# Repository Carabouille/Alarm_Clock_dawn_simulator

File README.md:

# Alarm_Clock_dawn_simulator
Hello, I'm Carabouille, a French guy who loves tech and hardware, and this is my GitHub to present you my project for Fallout!
I'm gonna present you my alarm clock with dawn simulator feature!

AND see just how beautiful it is !!! Yeah I know I did a great job you can tell me ^^

And to see how it works in details you can watch the video that I did on my alarm clock : (CLICK ON MY AWESOME FACE !)

# The idea 
I often have trouble waking up with my phone alarm. I often feel that I'm tired even though I slept a lot. And this is for a very simple reason: our brain is not a machine, he can't wake up so fast. He works on cycles. And our phone alarm gets him off very fast during this cycle. A better way to wake up more naturally is with the solar light (but the night I close the rolling shutter for the cold). So a solution to this issue is to use an alarm clocker with a dawn simulator feature to increase the brightness of the room over time to wake up your brain gently, but problem : Tis type of alarm clocks is really expensive (over 100 euros), so I told myself that it is the perfect occasion to create my own ALARM CLOCKS WITH A DAWN SIMULATOR!!! And I'm gonna add a lot of features like: 
- local weather
- Indoor temperature / humidity
- Bedside lamp (to read the night)
- Control all the Leds in my bedroom
- and more.....

I really can't wait to build my project, develop my skills and learn so much! I'm gonna give the best version of myself to be proud of my alarm clocks and I also hope that I will have the chance to go to Shenzen to meet other hardware fans! Kind regards, your French friend, Florian "Carabouille" CHARLES :))

# Zine page 
The better way to describe my project is with a poster who talks about it! 
I'm not a good designer, but I think that I made a good poster

ET VOILA : 

The design idea is pretty simple: the alarm clock in the center and some arrows to explain the different parts of the project
I explain here 7 features: 
- The oak log for the base
- All the PCBs
- The touch screen
- The Zen river
- The light for the dawn simulator feature
- The switch on the top
- And the switches and the knob on the side

My favourite color is the pink (hard to guess ^^)
I really love the cherry flower in the background that reminds me of the cherry tree on the top of the alarm.
The UwU logo is everywhere cause with my friends it's a private joke since a few years.
I love the way that the "Fallout" goes behind the box.

Is not perfect of course but for my light skills in design I think it's really nice, I'm proud of it ! 

# CAD 
One of the main parts of my project is the CAD!
For this I used the software Solidworks ( a French soft! COCORICO!)
I'm in a toxic relationship with Solidworks, sometimes I love it, sometimes I hate it...
This software is not easy to use but after some crashes and bugs I finally made a CAD which I'm proud of

So for my project I had to work within certain constraints 

- a specific screen size
- a way to diffuse the light
- a heat sink for the light
- some buttons
- a battery
- a speaker
- a hole for the USB C port

And with all that, I need to find a good idea for design

My first idea was a shape like the giant telescope, like we can see in the American desert.
But I have never obtained a result that I like

So I completely changed my idea to have a Zen garden on the top of my alarm clock
With a tree, plants, and a river!

It looks like this : 

yes that is not the same as on the zine page,
Solidworks is not really good at rendering

But all the parts are here and I even find it cool! 
I really love that the PCB is not hidden by all the cases, it's cool to see it

On this picture we can see : the screen, the PCB, the UwU logo, the oak log and the buttons on the side

If we move to the top we can see the Zen garden 

We can see :
- The hole on the top, for the cherry tree
- The river on the front
- The switch to shut down the alarm
- The green is for the artificial moss
- and the servo motor

The servo motor is here to hide the light during the day with moss on it. And when is it the time to turn the light on the servo motor move the piece of plastic with moss on it that hides the light to let the light illuminate the room.
So the light system is invisible during the day!

The servo motor is not hidden by the case cause the moss will recover it.

And on the switch I'll put a little Japanese temple like we can see on the poster.

Let's make the walls transparent to see what is inside the box!

Yes, there are a lot of things inside it! 

We can see well in the first picture the servo motor as we saw earlier
And the light with the heat sink, which is carried by a support with screws to the box
The heat sink is necessary here cause the light needs to be at least a 8W to diffuse a minimum of the light to wake you. 
But the light is also powered on 24V and if you do the calcul

P = U * I

I = P / U

I = 8 / 24 = 0,33 A 

It's a lot for a little LED COB ! It can heat up to more than 100 degrees. With the heat sink, everything will be ok!

If we watch the second picture we can see the other components

Like the speaker, even if the light is supposed to wake you. If you sleep very deeply, good music is necessary to wake up! 
We can see on the left the PCB buttons for all the buttons and the knob. Is linked with the main PCB with a FPC cable.

The huge tank in the middle is for the water of the river. The pump is also inside. The holes are for the pipes.

We can see the USB C port in the bottom right also linked with the main PCB with a FPC cable.

On the right we have the PCB for the SD card. And below it we have our battery.
The battery is just in case that there is a power cut at home, the battery will supply the system until the return of power !

And that's already a lot for a CAD, but I'm really proud of me! I can't wait to print it!

# PCB

OK so now it's the moment to talk about my PCB! And it's a huge part of my project! 
It's only my second PCB so it's not perfect, the first was the macropad.

This is only the main PCB, and I'm going to describe all the different parts
I'm not gonna describe how I chose the components because it's not really important, but for each component I had to follow the datasheet.

So we can see at the top left the port J1 that brings the power supply from the USB C port on an other PCB.
The power is sent to the first components the MCP73871. This component charge at the same time the battery in 4,2V and supplies the system with the 5V

But 5V is too high for an ESP32, so we need to decrease it to 3,3V with the AMS1117-3.3.

For this project I used an ESP32-S3-WROOM-1 that is very powerful and the WiFi connection will help me to search for the local weather.

For the speaker, we need to use an audio amplifier. I chose to use the MAX98357A, which is very famous for this type of project

I used a DW01A and a FS8205A, this duo of components is for the battery. To avoid overload, deep discharge, and protection from the short circuit.

For the LED and the fan of the heat sink I need 24V and 12V. So I used a 2 MT3608 to increase the voltage.

To control the led I'll use 2 channels of PWM to manage the warm and cold colors of the led.
To do this I'm gonna use a 2 transistors A03400A.

I also use a VEML770 a light sensor to manage the luminosity of the screen.

We also have a lot of connectors for the : 
- Screen
- USB C
- Heat sink
- Led COB
- Led strip (to decorate)
- servo motor
- SD card PCB
- Buttons PCB
- Battery

You can see two footprint for a switch (SW3 & SW4), if you wish to switch off the main power supply or just the battery power supply (!YOU NEED TO PLACE IT ! else the circuit is open)

And after having done the wiring diagram, it's time to root all the components between them! 

This is my final solution:

We can see here all the components which I mentioned earlier
I root on 2 faces so it's not too difficult to do it. The main difficulty is to match the footprint with the real component.

And that's all for the main PCB. It's already a lot!

Let's talk about the second PCB, The Buttons PCB!! 

This PCB is simpler than the previous one, it is just a little repetitive with all the buttons 
We can see here the wiring diagram!

You can see here 4 different PCBs separated by the blue lines.
The larger is the PCB with all the buttons and the polar.
Also, I used a MCP23017 to increase the number of pins GPIO of the ESP32 ( I used a lot of buttons ^^) I'll go into detail in the firmware part. 
You can see a capacitor in parallel for each button. It's anti-bounce material. It's very important for a professional project!
I added on this PCB an AHT 20, it's a temperature and humidity sensor.

The little PCB in the middle is for the switch on the top of the box.

The PCB on the bottom is the micro SD port card PCB

and the last is the PCB for the USB C

And after this it's rooting time ! 

That wasn't possible with the dimensions I needed to avoid the waste of some part of the PCB, like you can see the part not used.
I'm gonna cut the different PCB myself with a dremel.

# Firmware
The Firmware is a big part of my project! (I said it for each part ;-;)
To code I used the software Visual Studio Code and the extension Plateformio
The code is pretty simple for the moment. I only initialize all the components. I'm gonna add all the interesting features when I could have the card in my hands.
For the moment, given that I only initialize the components, all my code parts are just from the example code that I found online and from old code that I made.

In the code I initialize :
- The I2C bus
- The audio amplifier
- The SD card
- The screen
- The wifi connection (to obtain the hour, date and more soon)
- All the buttons with the MCP23017
- Servo motor
- the EC11
- The signal PWM for the LED
- The dislay of the hours on the screen
- The enable pin for the MT3608
- The VEML7700
- The AHT20

There are still a lot of things to add. I will add this later (with components in front of me) cause it is code more complicated, and it's useless to code this without debugging in live (I guess)

The things that I need to add: 
- A good design of the hours, temperatures, etc...
- alarm features (with the dawn simulator)
- all the buttons feature like :
- - turn on the smart plug of my computer
  - play a ACNL music
  - a sleep mode
  - song chill
  - bedside lamp
  - nap timer
  - switch that shuts down the alarm
  - set alarm 1
  - set alarm 2
  - turn on the leds of my room
  - turn on the river
  - the other buttons will be there to adjust certain settings

# BOM

Now it's the time to do the BOM and order all our components! 

I mainly used this site : 

- https://www.lcsc.com/ for the components CMD
- https://www.aliexpress.com for some electronics and decoration
- https://jlcpcb.com for the PCB

I split the BOM into different parts.

The first part is the components that I'm going to order on LCSC (Overall, these are the CMD components)

| Components LCSC :               | name                    | value           | Quantity | LCSC code / link        | price (€) |                                  |
|---------------------------------|-------------------------|-----------------|----------|-------------------------|-----------|----------------------------------|
|                                 | Resistance              | 100             | 1        | [C105588](https://www.lcsc.com/product-detail/C105588.html)            | 0.13      |       X                          |
|                                 |                         | 300             | 1        | [C2930092](https://www.lcsc.com/product-detail/C2930092.html)          | 0.12      | X                                |
|                                 |                         | 5,1k            | 2        | [C2907044](https://www.lcsc.com/product-detail/C2907044.html)                | 0.11      |       X                          |
|                                 |                         | 1M              | 1        | [C2907115](https://www.lcsc.com/product-detail/C2907115.html)                | 0.08      |    X                             |
|                                 |                         | 10k             | 11       | [C98220](https://www.lcsc.com/product-detail/C98220.html)                  | 0.28      |    X                             |
|                                 |                         | 180k            | 1        | [C2906999](https://www.lcsc.com/product-detail/C2906999.html)                | 0.1       |    X                             |
|                                 |                         | 1k              | 5        | [C22548](https://www.lcsc.com/product-detail/C22548.html)                  | 0.14      |    X                             |
|                                 |                         | 390k            | 1        | [C137735](https://www.lcsc.com/product-detail/C137735)                 | 0.15      |    X                             |
|                                 |                         | 2,2k            | 2        | [C4190](https://www.lcsc.com/product-detail/C4190.html)                   | 0.14      |    X                             |
|                                 | Capacitor               | 10n             | 2        | [C100042](https://www.lcsc.com/product-detail/C100042.html)                 | 0.23      |    X                             |
|                                 |                         | 100n            | 26       | [C14663](https://www.lcsc.com/product-detail/C14663.html)                  | 0.56      |    X                             |
|                                 |                         | 10u             | 4        | [C440198](https://www.lcsc.com/product-detail/C440198.html)                 | 1.27      |    X                             |
|                                 |                         | 1u              | 1        | [C28323](https://www.lcsc.com/product-detail/C28323.html)                  | 0.24      |    X                             |
|                                 |                         | 22u             | 5        | [C342620](https://www.lcsc.com/product-detail/C342620.html)                 | 2.1       |    X                             |
|                                 |                         | 4,7u            | 2        | [C98192](https://www.lcsc.com/product-detail/C98192.html)                  | 0.18      |    X                             |
|                                 | VEML7700-TT             | X               | 1        | [C1850416](https://www.lcsc.com/product-detail/C1850416.html)                | 1.49      |    X                             |
|                                 | FS8205A                 | X               | 1        | [C2830320](https://www.lcsc.com/product-detail/C2830320.html)                | 0.52      |    X                             |
|                                 | YLED0603B (led)         | Blue            | 1        | [C19171394](https://www.lcsc.com/product-detail/C19171394.html)               | 0.54      |    X                             |
|                                 | YLED0603G (led)         | Green           | 1        | [C19273151](https://www.lcsc.com/product-detail/C19273151.html)               | 0.54      |    X                             |
|                                 | KT-0603R (led)          | Red             | 1        | [C2286](https://www.lcsc.com/product-detail/C2286.html)                   | 0.59      |    X                             |
|                                 | MAX98357AETE+T          | X               | 1        | [C910544](https://www.lcsc.com/product-detail/C910544.html)                 | 1.24      |    X                             |
|                                 | MCP73871-2AAI/ML        | X               | 1        | [C144351](https://www.lcsc.com/product-detail/C144351.html)                 | 2.74      |    X                             |
|                                 | MT3608                  | X               | 2        | [C84817](https://www.lcsc.com/product-detail/C84817.html)                  | 0.69      |    X                             |
|                                 | SS14 (diode)            | X               | 2        | [C2837270](https://www.lcsc.com/product-detail/C2837270.html)                | 0.48      |    X                             |
|                                 | AHT20                   | X               | 1        | [C2757850](https://www.lcsc.com/product-detail/C2757850.html)                | 0.58      |    X                             |
|                                 | MCP23017T-E/ML          | X               | 1        | [C629439](https://www.lcsc.com/product-detail/C629439.html)                 | 1.46      |    X                             |
|                                 | micro sd card port      | X               | 1        | [C506790](https://www.lcsc.com/product-detail/C506790.html)                 | 3.66      |    X                             |
|                                 | USB-C port              | X               | 1        | [C2765186](https://www.lcsc.com/product-detail/C2765186.html)                | 1.17      |    X                             |
|                                 | DW01A                   | X               | 1        | [C351410](https://www.lcsc.com/product-detail/C351410.html)                 | 0.75      |    X                             |
|                                 | Coil                    | 22u             | 2        | [C2826664](https://www.lcsc.com/product-detail/C2826664.html)                | 0.64      |    X                             |
|                                 | AMS1117-3.3             | X               | 1        | [C6186](https://www.lcsc.com/product-detail/C6186.html)                   | 0.99      |    X                             |
|                                 | AO3400A                 | X               | 2        | [C20917](https://www.lcsc.com/product-detail/C20917.html)                  | 0.36      |    X                             |
|                                 | FFC / FPC connector 1mm | 8 pins          | 4        | [C262714](https://www.lcsc.com/product-detail/C262714.html)                 | 0.99      |    X                             |
|                                 |                         | 12 pins         | 2        | [C262718](https://www.lcsc.com/product-detail/C262718.html)                 | 1.1       |    X                             |
|                                 | ESP32-S3-WROOM-1        | X               | 1        | [C2913202](https://www.lcsc.com/product-detail/C2913202.html)                | 4.58      |    X                             |
|      Total                      |                         |                 |          |                         | 30.94     |                                 |
|                                 |                         |                 |          |                         |           |                                 |

The second part is for the other types of components like switch, pump, speaker, LED, etc...
For the moment, it's only electronic components, all buy in Aliexpress

| Components               | name                    | value           | Quantity | LCSC code / link        | price (€) |                                  |
|---------------------------------|-------------------------|-----------------|----------|-------------------------|-----------|----------------------------------|
| Others components (not in LCSC) | Switch push buttons     | 6mm.6mm.5.5mm   | 17       | [Link](https://fr.aliexpress.com/item/1005001629177989.html)                    | 1.22      |                                  |
|                                 | EC11 rotary encoder     | X               | 1        | [Link](https://fr.aliexpress.com/item/1005003824684681.html)                    | 1.33      |                                  |
|                                 | Touch screen            | 4 inch          | 1        | [Link](https://fr.aliexpress.com/item/1005005791515997.html)                    | 14.39     |                                  |
|                                 | Speaker                 | 8 ohm           | 1        | [Link](https://fr.aliexpress.com/item/4000034945525.html)                    | 10.7      |                                  |
|                                 | keyboard switch         | X               | 1        | [Link](https://fr.aliexpress.com/item/1005006298192363.html)                     | 4.39      |                                  |
|                                 | Servo motor             | 180 degrees     | 1        | [Link](https://fr.aliexpress.com/item/1005006572297006.html)                      | 2.7       |                                  |
|                                 | LED COB                 | 24V 8W          | 1        | [Link](https://fr.aliexpress.com/item/1005006373977700.html)                      | 1.89      |        X                         |
|                                 | Heat sink               | with fan 12V    | 1        | [Link](https://fr.aliexpress.com/item/1005003605697738.html)                      | 3.19      |                                  |
|                                 | Male pins               | 17 pins         | 1        | [Link](https://fr.aliexpress.com/item/4000873858801.html)                      | 1.89      |     X                            |
|                                 | Female pins             | 14 pins         | 1        |                         |           |      X                           |
|                                 | Battery                 | 18650           | 1        | [Link](https://fr.aliexpress.com/item/1005008704468583.html)                      | 6.59      |                                  |
|                                 | Led strip               | addressable 1m  | 1        | [Link](https://fr.aliexpress.com/item/1005009613294814.html)                      | 4.99      |                                  |
|                                 | 3D-printed insert       | M3              | 12       | [Link](https://fr.aliexpress.com/item/1005007653131713.html)                      | 1.69      |                                  |
|                                 | Screw                   | M3              | 12       | [Link](https://fr.aliexpress.com/item/32968616563.html)                      | 1.4       |                                  |
|                                 | Micro SD card           | 4go             | 1        | [Link](https://fr.aliexpress.com/item/1005008059516973.html)                      | 3.29      |                                  |
|                                 | FPC cable               | 12pins 15cm 1mm | 1        | [Link](https://fr.aliexpress.com/item/1005007561337665.html)                      | 1.72      |        X                         |
|                                 |                         | 8pins 10cm 1mm  | 2        | [Link](https://fr.aliexpress.com/item/1005007561337665.html)                      | 2.18      |        X                         |
|                                 | epoxy resin             | 50ml + 50ml     | 1        | [Link](https://fr.aliexpress.com/item/1005007345256355.html)                      | 6.59      |        X                         |
|                                 | Water pump              | 5V              | 1        | [Link](https://fr.aliexpress.com/item/1005006614378374.html)                      | 1.69      |        X                         |
|                                 | Pipe                    | 1m              | 1        | [Link](https://fr.aliexpress.com/item/1005006614378374.html)                      | 1.81      |        X                         |
|                                 | Switch                 | ON OFF ON              | 2        | [Link](https://fr.aliexpress.com/item/1005002461701337.html)                      | 2.4      |                                 |
|                     Total       |                         |                 |          |                         | 73.65     |                                  |
|                                 |                         |                 |          |                         |           |                                  |

In this last part we have the PCB, and all the elements of decoration 

| Components               | name                    | value           | Quantity | LCSC code / link        | price (€) |                                  |
|---------------------------------|-------------------------|-----------------|----------|-------------------------|-----------|----------------------------------|
| PCB (JLCPCB)                    | Main PCB                | X               | 1        | Upload GERBER on JLCPCB | 3.4       | X                                |
|                                 | Buttons PCB             | X               | 1        |                         | 3.4       |  X                               |
|                                 |                         |                 |          |                         |           |                                 |
| Décoration                      | Log (for the base)      | 14-16cm         | 2        | [Link](https://fr.aliexpress.com/item/1005007635992230.html)                      | 9.78      |                                X |
|                                 | Temple                  | X               | 1        | [Link](https://fr.aliexpress.com/item/1005007500230985.html)                      | 2.1       |                                X |
|                                 | Moss 1                  | 20g             | 1        | [Link](https://fr.aliexpress.com/item/1005005026348059.html)                      | 1.72      |                                X |
|                                 | Moss 2                  | 20g             | 1        | [Link](https://fr.aliexpress.com/item/1005005026348059.html)                      | 2.04      |                                X |
|                                 | Cherry tree             | X               | 1        | [Link](https://fr.aliexpress.com/item/1005003593401791.html)                      | 3.89      |                                X |
|                                 | PLA black + white       | 1kg + 1kg       | 1        | [Link](https://www.amazon.fr/gp/product/B0CV4V5L7T/ref=ewc_pr_img_1?smid=AKWYTSYUMR87P&th=1)                      | 20.12     |                                X |
|                                 | Bridge                  | X               | 1        | [Link](https://fr.aliexpress.com/item/1005003493992894.html)                      | 1.05      |                                X |
|                  Total          |                         |                 |          |                         | 42.7      |                                  |
|                                 |                         |                 |          |                         |           |                                  |
|                                 |                         |                 |          |                         |           |                                  |
| Full price                      | 153.94                  |                 |          |                         |           |                                  |

So the total for all this is 153,94€ (180,55$)

# Build it ! 

To build this you first need to order all the components that you need. 

After this it's time to print the box and all the others parts who are in the STL file. For the color : withe for the box, black for the buttons and the UwU eyes and pink for the knob et the UwU cheeks. for the support inside the box it's doesn't matter.

You need to apply the epoxy resin on all the surfaces in direct contact with the water (like the river and the tank)

Glue the log on the underside of the box 

You need to solder all the components on the pcb (following the wiring diagram (view it on the kicad files)), and solder the external components (like the speaker, battery, etc) 

Upload the code on the ESP32.

Following that you need to setup all the components inside the box like the CAD 

Holes are here to support the support of the switch and the heat sink on the top of the box with screw M3.

Place all the decoration elements on the top (like the moss, the tree, the temple, etc..)

And after that You need to setup the timer of the alamr clock and that's ALL ! 

# Special thanks

I want to thank my friend Pylou (love u my boy) for introducing me to the project !!

thanks to the HackClub / Fallout community the goatest community 

thanks to my mum for creating me

Thanks to photosynthesis for creating the oxygen that I breathe

Thanks to the reviewer !! I know the project is not easy to understand ;-; 

Thanks to Soup for the free koi with the streak ! 

I really hope you will enjoy it !

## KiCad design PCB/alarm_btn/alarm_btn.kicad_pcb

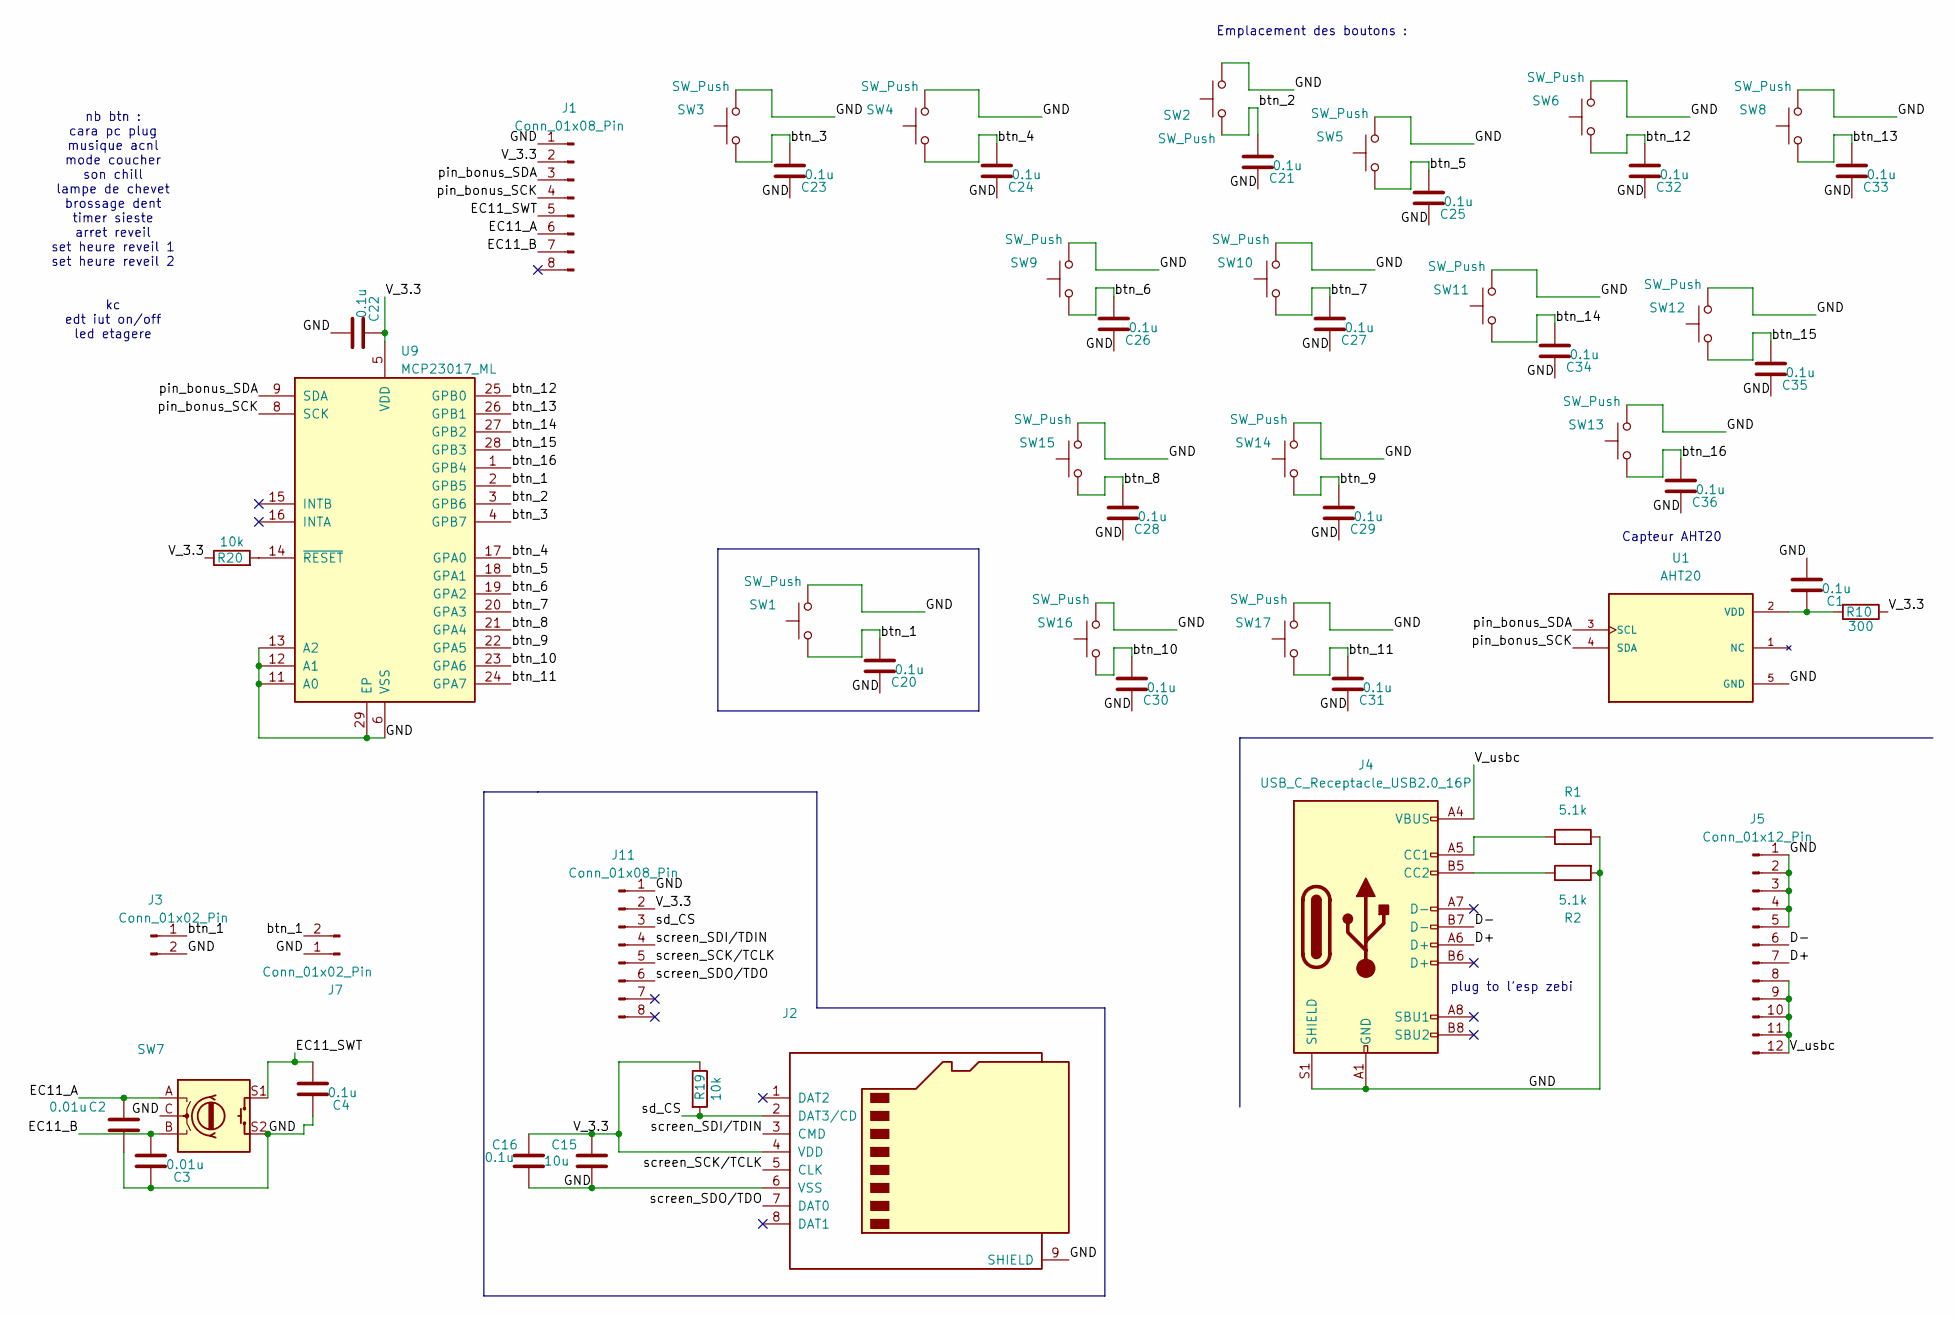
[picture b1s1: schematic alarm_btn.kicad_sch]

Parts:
C1, C4, C16, C20, C21, C22, C23, C24, C25, C26, C27, C28, C29, C30, C31, C32, C33, C34, C35, C36: 0.1u; C_0603_1608Metric; LCSC C14663
C2, C3: 0.01u; C_0603_1608Metric; LCSC C100042
C15: 10u; C_0805_2012Metric; LCSC C440198
J1, J11: Conn_01x08_Pin; JUSHUO_AFA07-S08FCA-00_1x8-1MP_P1.0mm_Horizontal; LCSC C262714
J2: Micro_SD_Card; SD_Hirose_DM1AA_SF_PEJ82; LCSC C506790
J3, J7: Conn_01x02_Pin; PinHeader_1x02_P2.54mm_Vertical
J4: USB_C_Receptacle_USB2.0_16P; USB_C_Receptacle_HRO_TYPE-C-31-M-12; LCSC C2765186
J5: Conn_01x12_Pin; JUSHUO_AFA07-S12FCA-00_1x12-1MP_P1.0mm_Horizontal; LCSC C262718
R1, R2: 5.1k; R_0603_1608Metric
R10: 300; R_0603_1608Metric; LCSC C2930092
R19, R20: 10k; R_0603_1608Metric; LCSC C98220
SW1: SW_Push; SW_Cherry_MX_1.00u_PCB
SW2, SW3, SW4, SW5, SW6, SW8, SW9, SW10, SW11, SW12, SW13, SW14, SW15, SW16, SW17: SW_Push; SW_PUSH_6mm
SW7: RotaryEncoder_Switch; RotaryEncoder_Alps_EC11E-Switch_Vertical_H20mm
U1: AHT20; PSON100P300X300X110-6N; PARTREV V1.0; LCSC C2757850
U9: MCP23017_ML; QFN-28-1EP_6x6mm_P0.65mm_EP4.25x4.25mm; LCSC C629439

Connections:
/D+: J4.A6 (D+), J5.7
/D-: J4.B7 (D-), J5.6
/EC11_A: C2.1, J1.6, SW7.A
/EC11_B: C3.1, J1.7, SW7.B
/EC11_SWT: C4.2, J1.5, SW7.S1
/GND: C1.2, C2.2, C3.2, C4.1, C15.1, C16.2, C20.1, C21.1, C22.2, C23.1, C24.1, C25.1, C26.1, C27.1, C28.1, C29.1, C30.1, C31.1, C32.1, C33.1, C34.1, C35.1, C36.1, J1.1, J2.6 (VSS), J2.9 (SHIELD), J3.2, J4.A1 (GND), J4.A12 (GND), J4.B1 (GND), J4.B12 (GND), J4.S1 (SHIELD), J5.1, J5.2, J5.3, J5.4, J5.5, J7.1, J11.1, R1.2, R2.2, SW1.2, SW2.1, SW3.2, SW4.2, SW5.2, SW6.2, SW7.C, SW7.S2, SW8.2, SW9.2, SW10.2, SW11.2, SW12.2, SW13.2, SW14.2, SW15.2, SW16.2, SW17.2, U1.5 (GND), U9.6 (VSS), U9.11 (A0), U9.12 (A1), U9.13 (A2), U9.29 (EP)
/V_3.3: C15.2, C16.1, C22.1, J1.2, J2.4 (VDD), J11.2, R10.1, R19.1, R20.1, U9.5 (VDD)
/V_usbc: J4.A4 (VBUS), J4.A9 (VBUS), J4.B4 (VBUS), J4.B9 (VBUS), J5.8, J5.9, J5.10, J5.11, J5.12
/btn_1: C20.2, J3.1, J7.2, SW1.1, U9.2 (GPB5)
/btn_2: C21.2, SW2.2, U9.3 (GPB6)
/btn_3: C23.2, SW3.1, U9.4 (GPB7)
/btn_4: C24.2, SW4.1, U9.17 (GPA0)
/btn_5: C25.2, SW5.1, U9.18 (GPA1)
/btn_6: C26.2, SW9.1, U9.19 (GPA2)
/btn_7: C27.2, SW10.1, U9.20 (GPA3)
/btn_8: C28.2, SW15.1, U9.21 (GPA4)
/btn_9: C29.2, SW14.1, U9.22 (GPA5)
/btn_10: C30.2, SW16.1, U9.23 (GPA6)
/btn_11: C31.2, SW17.1, U9.24 (GPA7)
/btn_12: C32.2, SW6.1, U9.25 (GPB0)
/btn_13: C33.2, SW8.1, U9.26 (GPB1)
/btn_14: C34.2, SW11.1, U9.27 (GPB2)
/btn_15: C35.2, SW12.1, U9.28 (GPB3)
/btn_16: C36.2, SW13.1, U9.1 (GPB4)
/pin_bonus_SCK: J1.4, U1.4 (SDA), U9.8 (SCK)
/pin_bonus_SDA: J1.3, U1.3 (SCL), U9.9 (SDA)
/screen_SCK/TCLK: J2.5 (CLK), J11.5
/screen_SDI/TDIN: J2.3 (CMD), J11.4
/screen_SDO/TDO: J2.7 (DAT0), J11.6
/sd_CS: J2.2 (DAT3/CD), J11.3, R19.2
unnamed: J4.A5 (CC1), R1.1
unnamed: J4.B5 (CC2), R2.1
unnamed: C1.1, R10.2, U1.2 (VDD)
unnamed: R20.2, U9.14 (~RESET)

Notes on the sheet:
Capteur AHT20
Emplacement des boutons :
nb btn : cara pc plug musique acnl mode coucher son chill lampe de chevet brossage dent timer sieste arret reveil set heure reveil 1 set heure reveil 2 kc edt iut on/off led etagere
plug to l'esp zebi

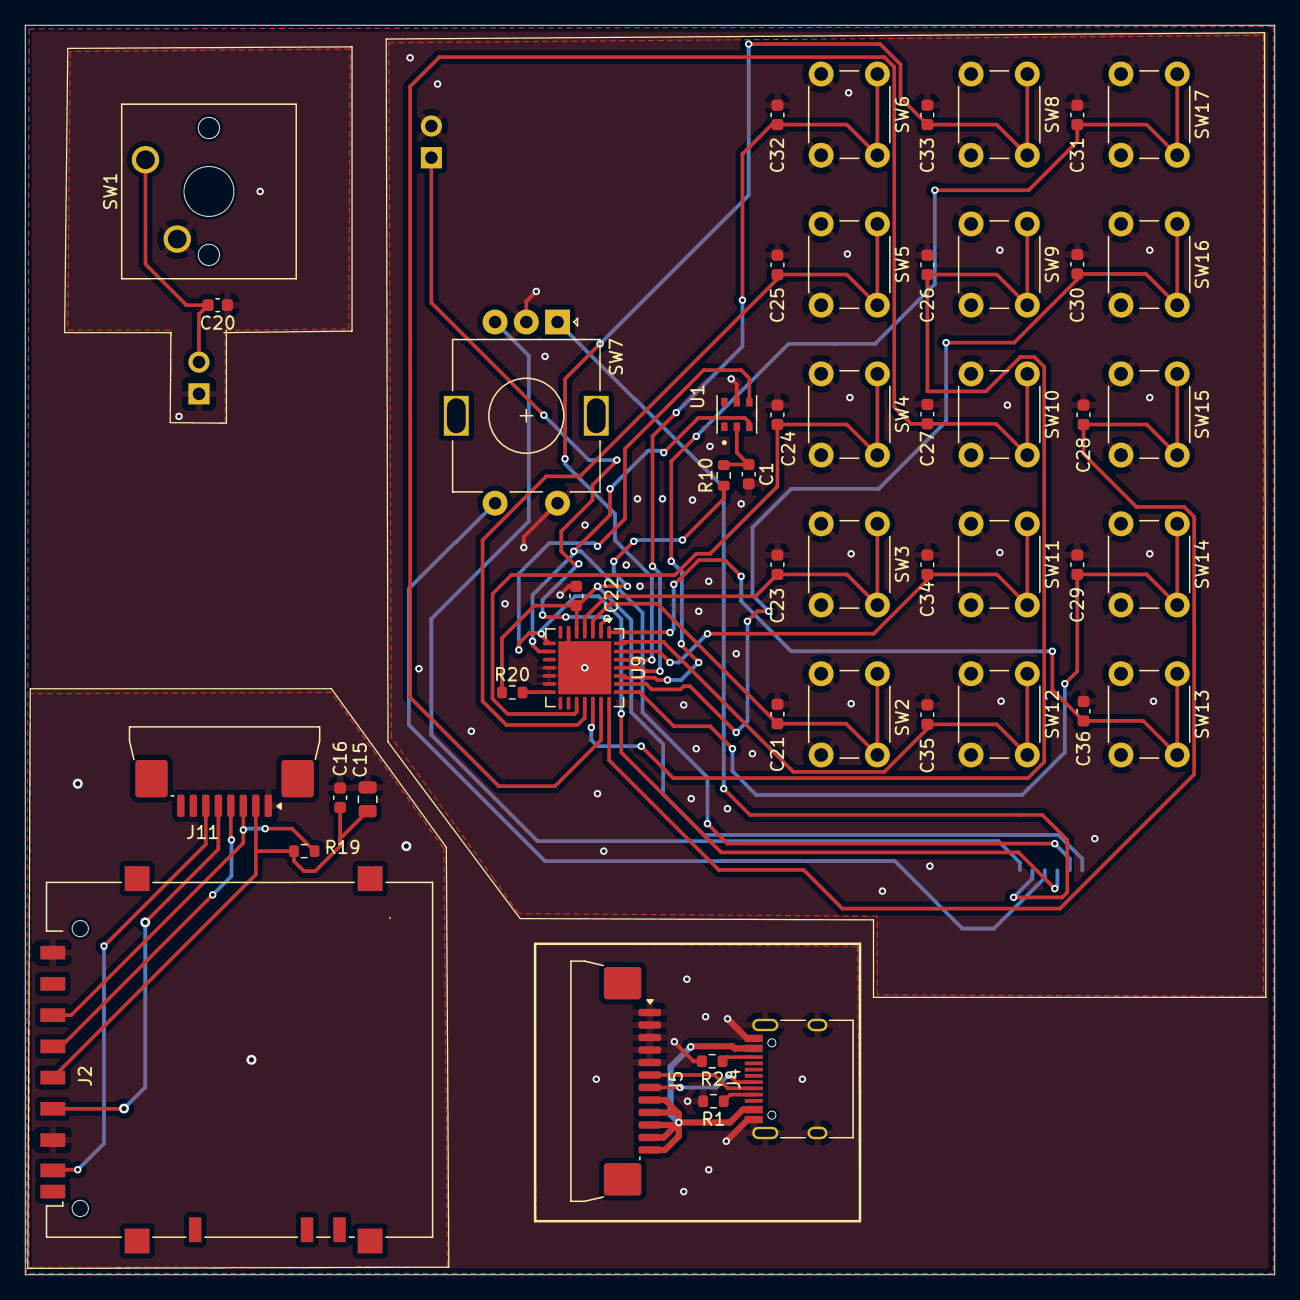
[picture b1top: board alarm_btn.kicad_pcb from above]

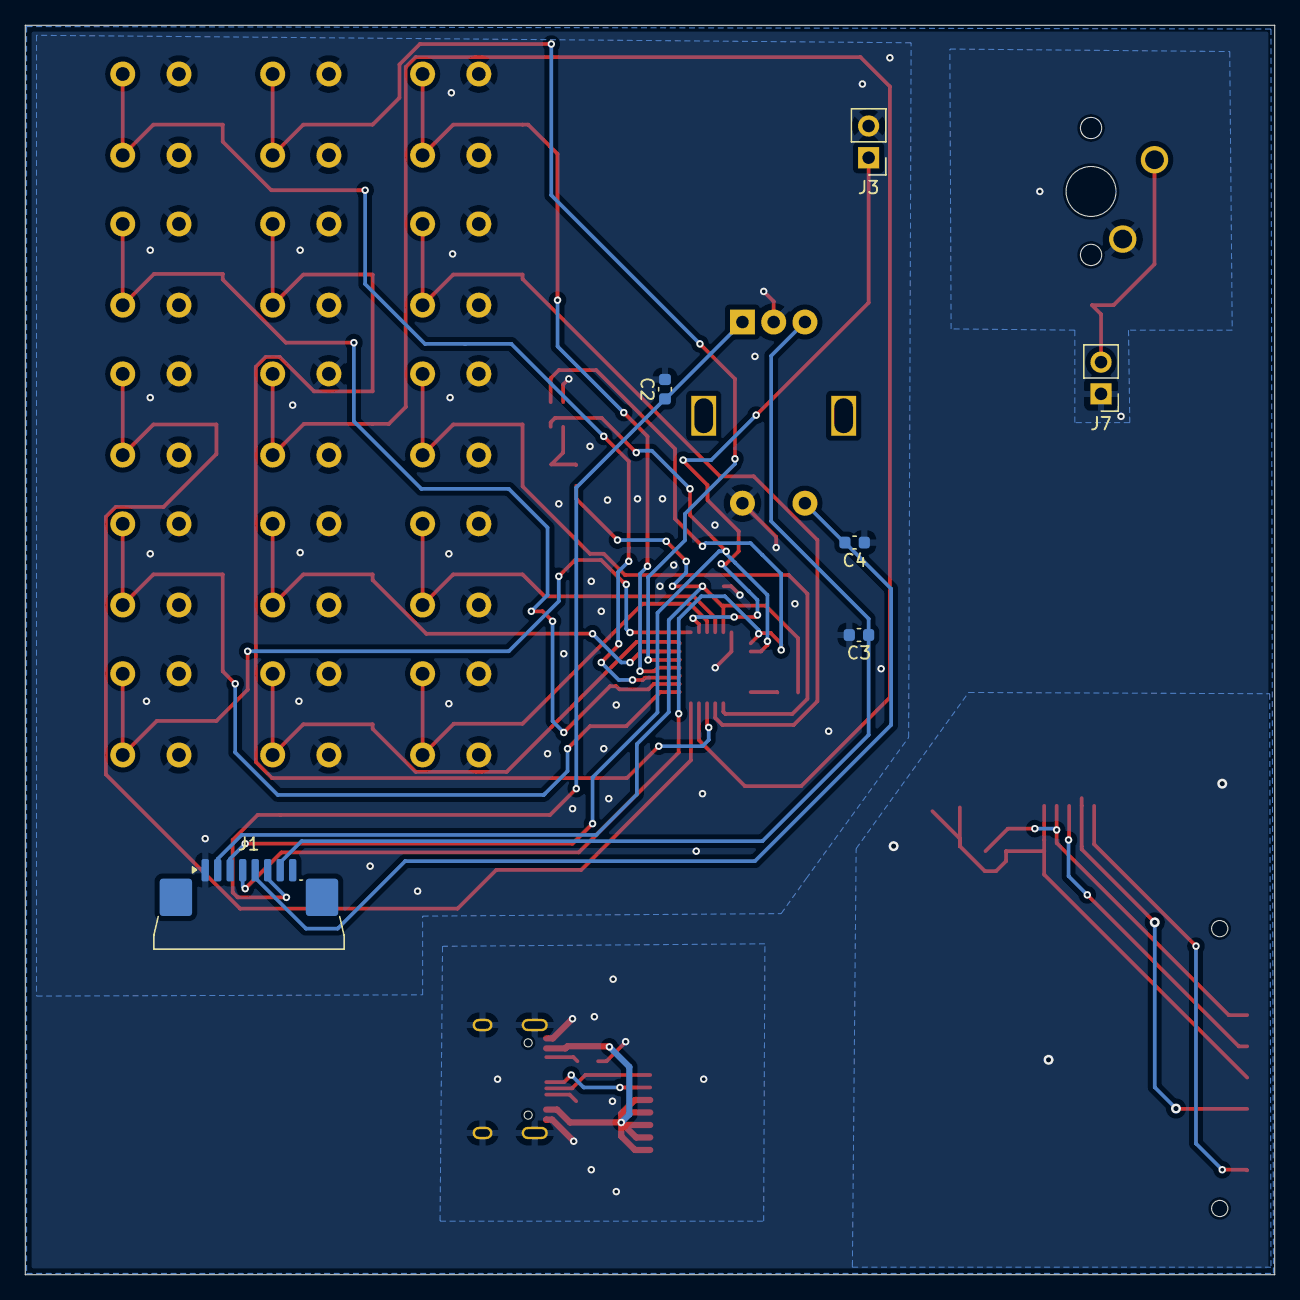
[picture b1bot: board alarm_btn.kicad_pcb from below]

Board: 2 copper layers, 100.0 x 100.0 mm, 54 parts (6 on the bottom side), 34 nets.

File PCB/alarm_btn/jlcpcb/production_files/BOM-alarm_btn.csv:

Comment,Designator,Footprint,LCSC,Quantity
0.01u,"C2,C3",C_0603_1608Metric,C100042,2
0.1u,"C1,C16,C20,C21,C22,C23,C24,C25,C26,C27,C28,C29,C30,C31,C32,C33,C34,C35,C36,C4",C_0603_1608Metric,C14663,20
10k,"R19,R20",R_0603_1608Metric,C98220,2
10u,C15,C_0805_2012Metric,C440198,1
300,R10,R_0603_1608Metric,C2930092,1
5.1k,"R1,R2",R_0603_1608Metric,C2907044,2
AHT20,U1,PSON100P300X300X110-6N,C2757850,1
Conn_01x08_Pin,"J1,J11",JUSHUO_AFA07-S08FCA-00_1x8-1MP_P1.0mm_Horizontal,C262714,2
Conn_01x12_Pin,J5,JUSHUO_AFA07-S12FCA-00_1x12-1MP_P1.0mm_Horizontal,C262718,1
MCP23017_ML,U9,QFN-28-1EP_6x6mm_P0.65mm_EP4.25x4.25mm,C629439,1
Micro_SD_Card,J2,SD_Hirose_DM1AA_SF_PEJ82,C506790,1
USB_C_Receptacle_USB2.0_16P,J4,USB_C_Receptacle_HRO_TYPE-C-31-M-12,C2765186,1

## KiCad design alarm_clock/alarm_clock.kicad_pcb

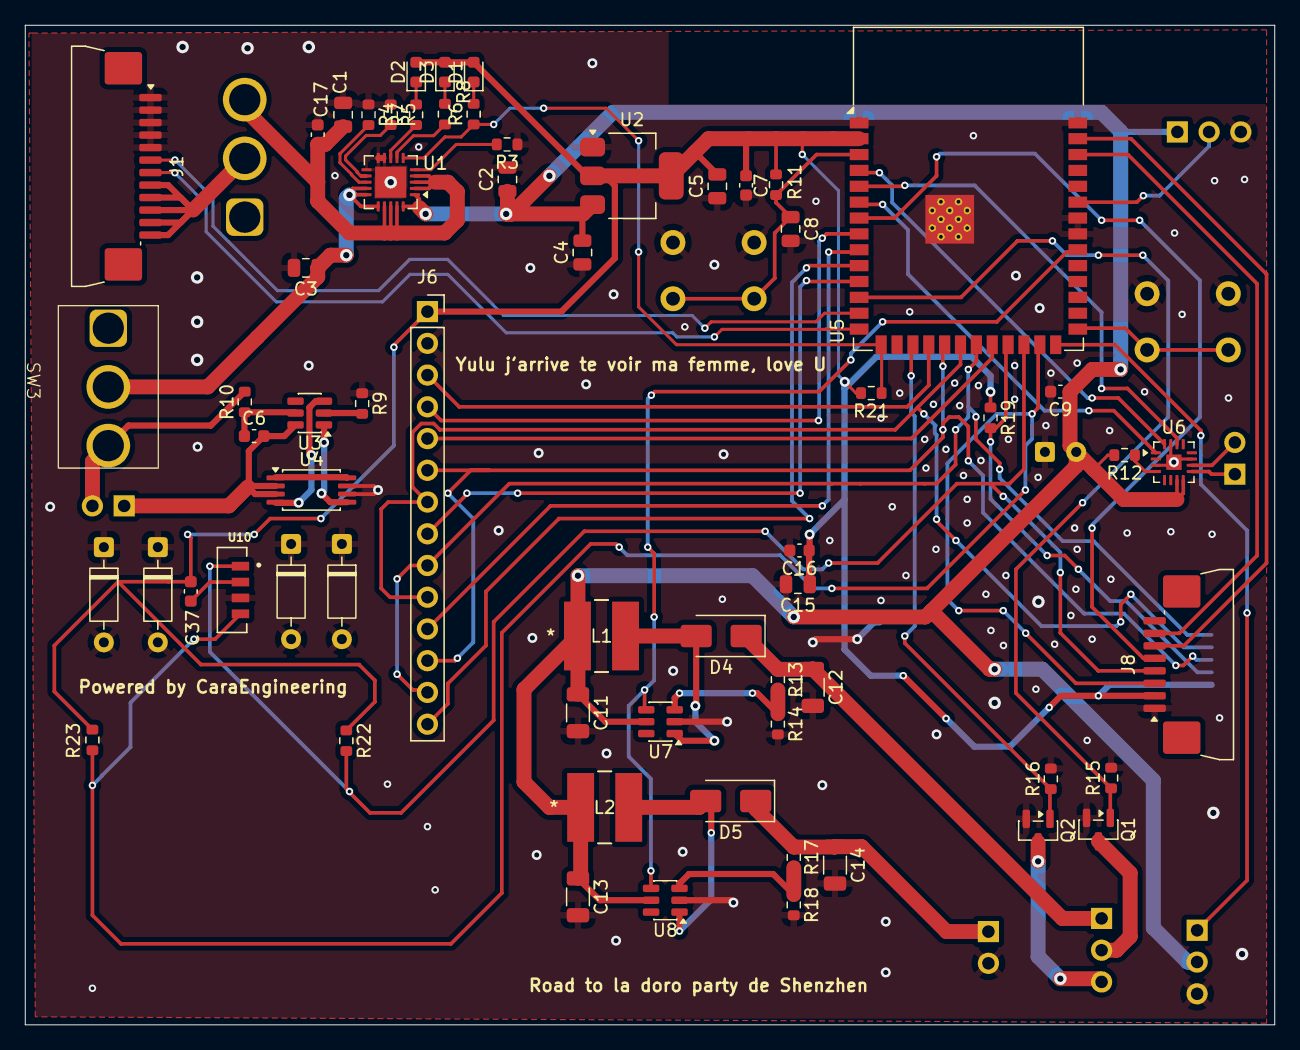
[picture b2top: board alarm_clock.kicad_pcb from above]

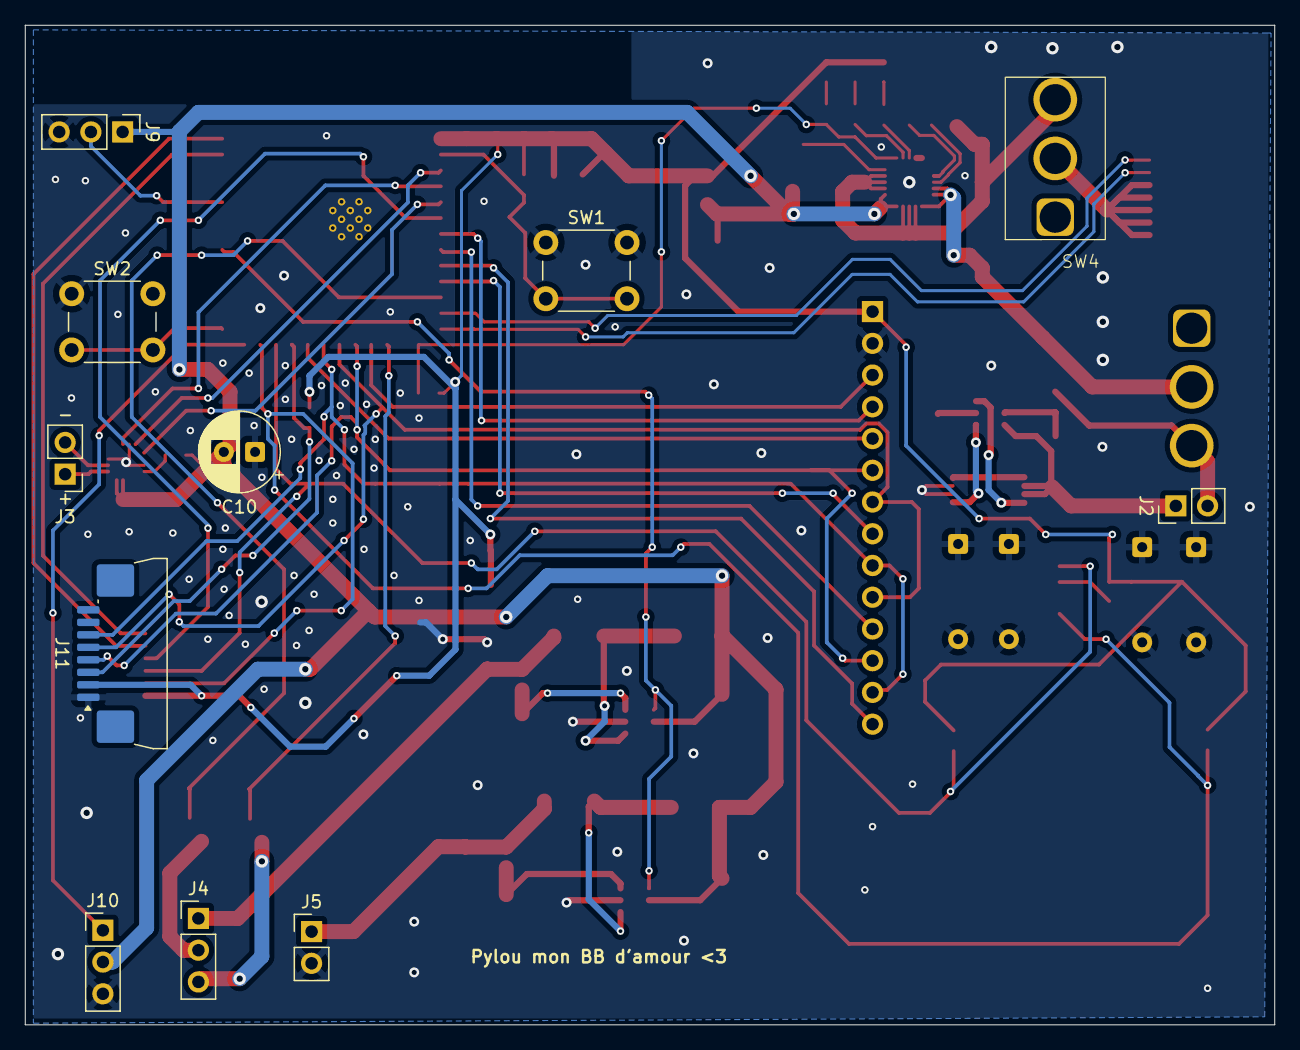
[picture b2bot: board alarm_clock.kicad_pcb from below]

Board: 2 copper layers, 100.0 x 80.0 mm, 74 parts (11 on the bottom side), 61 nets.

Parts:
C1, C4, C15: 10u; C_0805_2012Metric
C2, C3: 4.7u; C_0805_2012Metric
C5: 22u; C_0805_2012Metric
C6, C7, C9, C16, C17, C37: 0.1u; C_0603_1608Metric
C8: 1u; C_0805_2012Metric
C10: 470u; CP_Radial_D6.3mm_P2.50mm
C11, C12, C13, C14: 22u; C_1206_3216Metric
D1, D2, D3: LED; LED_0603_1608Metric
D4, D5: SS14; D_SMA
D15, D15#2, D15#3, D15#4: 1N4148; D_DO-35_SOD27_P7.62mm_Horizontal
J1: Conn_01x12_Pin; JUSHUO_AFA07-S12FCA-00_1x12-1MP_P1.0mm_Horizontal
J2, J3, J5: Conn_01x02_Pin; PinHeader_1x02_P2.54mm_Vertical
J4, J9, J10: Conn_01x03_Pin; PinHeader_1x03_P2.54mm_Vertical
J6: Conn_01x14_Socket; PinSocket_1x14_P2.54mm_Vertical
J8, J11: Conn_01x08_Pin; JUSHUO_AFA07-S08FCA-00_1x8-1MP_P1.0mm_Horizontal
L1, L2: 22u; IND_CD54_SUM
Q1, Q2: AO3400A; SOT-23
R3, R5, R11, R14, R15, R16, R18, R19, R21: 10k; R_0603_1608Metric
R4, R6, R7, R8, R9: 1k; R_0603_1608Metric
R10: 100; R_0603_1608Metric
R12: 1000k; R_0603_1608Metric
R13: 390k; R_0603_1608Metric
R17: 180k; R_0603_1608Metric
R22, R23: 2.2k; R_0603_1608Metric
SW1, SW2: SW_Push; SW_PUSH_6mm
SW3, SW4: SW_SPDT; switch_on_on
U1: MCP73871-2AA; QFN-20-1EP_4x4mm_P0.5mm_EP2.5x2.5mm
U2: AMS1117-3.3; SOT-223-3_TabPin2
U3: DW01A; SOT-23-6
U4: FS8205A; TSSOP-8_4.4x3mm_P0.65mm
U5: ESP32-S3-WROOM-1
U6: MAX98357A; TQFN-16-1EP_3x3mm_P0.5mm_EP1.23x1.23mm
U7, U8: MT3608; SOT-23-6
U10: VEML770; XDCR_VEML7700-TR

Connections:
/D+: J1.7, U5.14 (USB_D+)
/D-: J1.6, U5.13 (USB_D-)
/EC11_A: J8.6, U5.39 (IO1)
/EC11_B: J8.7, U5.38 (IO2)
/EC11_SWT: J8.5, U5.7 (IO7)
/EN_FAN_LED: U5.32 (IO39), U7.4 (EN), U8.4 (EN)
/GND: C1.1, C2.2, C3.2, C4.1, C5.1, C7.2, C8.2, C9.2, C10.1, C11.2, C12.2, C13.2, C14.2, C15.2, C16.2, C17.1, D15.1 (K), D15.2 (A), D15#2.1 (K), D15#2.2 (A), D15#3.1 (K), D15#3.2 (A), D15#4.1 (K), D15#4.2 (A), J1.1, J1.2, J1.3, J1.4, J1.5, J5.2, J6.2, J8.1, J9.3, J10.3, J11.1, Q1.2 (S), Q2.2 (S), R3.1, R4.1, R5.1, R9.1, R14.2, R15.2, R16.2, R18.2, SW1.1, SW2.1, U1.9 (~TE), U1.10 (V_{SS}), U1.11 (V_{SS}), U1.21 (V_{SS}), U2.1 (GND), U4.6 (S2), U4.7 (S2), U5.1 (GND), U5.33 (IO40), U5.34 (IO41), U5.40 (GND), U5.41 (GND), U6.3 (GND), U6.11 (GND), U6.15 (GND), U6.17 (PAD), U7.2 (GND), U8.2 (GND), U10.3 (GND)
/I2S_BCLK: U5.4 (IO4), U6.16 (BCLK)
/I2S_DIN: U5.6 (IO6), U6.1 (DIN)
/I2S_LRC: U5.5 (IO5), U6.14 (LRCLK)
/PWM_LEDA: Q1.1 (G), R15.1, U5.12 (IO8)
/PWM_LEDB: Q2.1 (G), R16.1, U5.17 (IO9)
/V_3.3: C5.2, C7.1, C15.1, C16.1, C37.2, D1.2 (A), D2.2 (A), D3.2 (A), J6.1, J8.2, J11.2, R11.2, R19.1, R21.2, R22.1, R23.1, U2.2 (VO), U5.2 (3V3)
/V_12V: C14.1, D5.1 (K), J5.1, R17.1
/V_24V: C12.1, D4.1 (K), J4.1, R13.1
/V_bat: C3.1, SW3.2 (B), U1.14 (V_{BAT}), U1.15 (V_{BAT}), U1.16 (V_{BAT_SENSE})
/V_bat+_afterswitch: J2.2, R10.2, SW3.3 (C)
/V_bat-: C6.2, J2.1, U3.6 (GND), U4.2 (S1), U4.3 (S1)
/V_ledA: J4.2, Q1.3 (D)
/V_ledB: J4.3, Q2.3 (D)
/V_servo_moteur: J10.1, U5.26 (IO45)
/V_state_usb: R6.1, R21.1, U1.6 (~PG), U5.15 (IO3)
/V_sys: C2.1, C4.2, C9.1, C10.2, C11.1, C13.1, J9.1, J10.2, L1.1, L2.1, R12.2, U1.1 (OUT), U1.20 (OUT), U2.3 (VI), U6.7 (VDD), U6.8 (VDD), U7.5 (IN), U8.5 (IN)
/V_usbc: J1.8, J1.9, J1.10, J1.11, J1.12, SW4.2 (B)
/V_usbc1: C1.2, C17.2, SW4.3 (C), U1.2 (VPCC), U1.3 (SEL), U1.4 (PROG2), U1.17 (CE), U1.18 (IN), U1.19 (IN)
/deco_led: J9.2, U5.35 (IO42)
/pin_bonus_SCK: J8.4, R22.2, U5.24 (IO47), U10.1 (SCL)
/pin_bonus_SDA: J8.3, R23.2, U5.25 (IO48), U10.4 (SDA)
/screen_CS: J6.3, U5.18 (IO10)
/screen_DC: J6.5, U5.22 (IO14)
/screen_SCK/TCLK: J6.7, J6.10, J11.5, U5.20 (IO12)
/screen_SDI/TDIN: J6.6, J6.12, J11.4, U5.19 (IO11)
/screen_SDO/TDO: J6.9, J6.13, J11.6, U5.21 (IO13)
/screen_TCS: J6.11, U5.9 (IO16)
/screen_TIRQ: J6.14, U5.10 (IO17)
/screen_led: J6.8, U5.11 (IO18)
/screen_reset: J6.4, U5.8 (IO15)
/sd_CS: J11.3, R19.2, U5.23 (IO21)
unnamed: D1.1 (K), R6.2
unnamed: D2.1 (K), R7.2
unnamed: D3.1 (K), R8.2
unnamed: D4.2 (A), L1.2, U7.1 (SW)
unnamed: D5.2 (A), L2.2, U8.1 (SW)
unnamed: J3.1, U6.9 (OUTP)
unnamed: J3.2, U6.10 (OUTN)
unnamed: R4.2, U1.13 (PROG1)
unnamed: R5.2, U1.12 (PROG3)
unnamed: R7.1, U1.8 (STAT1/~LBO)
unnamed: R8.1, U1.7 (STAT2)
unnamed: R3.2, U1.5 (THERM)
unnamed: R9.2, U3.2 (CS)
unnamed: U3.3 (OC), U4.4 (G1)
unnamed: U3.1 (OD), U4.5 (G2)
unnamed: C6.1, R10.1, U3.5 (VCC)
unnamed: U4.1 (D1), U4.8 (D2)
unnamed: C8.1, R11.1, SW1.2, U5.3 (EN)
unnamed: SW2.2, U5.27 (IO0)
unnamed: R12.1, U6.4 (~SD_MODE)
unnamed: R13.2, R14.1, U7.3 (FB)
unnamed: R17.2, R18.1, U8.3 (FB)
unnamed: C37.1, U10.2 (VDD)

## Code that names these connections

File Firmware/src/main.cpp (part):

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

//GESTION AUDIO
#define SD_CS_PIN 23

#define I2S_BCLK_PIN 4
#define I2S_LRC_PIN  5 
#define I2S_DOUT_PIN 6
Audio audio;

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 Serial.println("\n--- Test Audio : ESP32-audioI2S ---");

  // 1. Initialisation de la carte SD
  if (!SD.begin(SD_CS_PIN)) {
    Serial.println("ERREUR : SD introuvable !");
    while(1); 
  }
  Serial.println("SD OK !");
  
  audio.setPinout(I2S_BCLK_PIN, I2S_LRC_PIN, I2S_DOUT_PIN);
  
  // volume de 0 à 21
  audio.setVolume(5); 
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
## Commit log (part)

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2026-04-20 Create CAD
2026-04-20 Create folder
2026-04-21 Envoi propre des fichiers 3D avec LFS
2026-04-21 Rename Assemblage1.SLDASM to CAO/Assemblage1.SLDASM
2026-04-21 Assemblage
2026-04-21 Fix image path in README.md
2026-04-21 Correct image tag for alarm clock poster
    Fix image tag formatting in README.
2026-04-21 Update README with power and current calculations
    Added calculations for current and power requirements for the light.
2026-04-22 Expand README with project component details
    Added details about components used in the project, including audio amplifier, battery protection, voltage regulation, PWM control for LEDs, light sensor, and connectors.
2026-04-22 Expand BOM section with component details and costs
    Added detailed breakdown of BOM components and costs, including images and notes on sourcing from LCSC and Aliexpress.
2026-04-24 Fix typos and improve readability in README
    Corrected grammar, punctuation, and spelling errors throughout the README file for improved clarity and readability.
2026-04-24 Improve README introduction and remove redundancy
    Revised the introduction for clarity and removed redundancy.
2026-04-24 Update features list in README
    Removed mention of battery from features list.
2026-04-24 Rename Assemblage1.SLDASM to Box_assembled.SLDASM
2026-04-24 Fix typo in README.md regarding future meeting
2026-04-25 Clean up components table in README
    Removed unnecessary 'X' from the components table.
2026-04-30 Ajout du fichier STEP
2026-04-30 Add STEP
2026-06-25 Enhance README with personal introduction and image
    Added a personal touch and image to the project description.
2026-06-25 Change video link in README.md
    Updated video link to a YouTube short for better accessibility.
2026-06-25 Enhance README with video link and description
    Updated the README to include a clickable video link for demonstration.
